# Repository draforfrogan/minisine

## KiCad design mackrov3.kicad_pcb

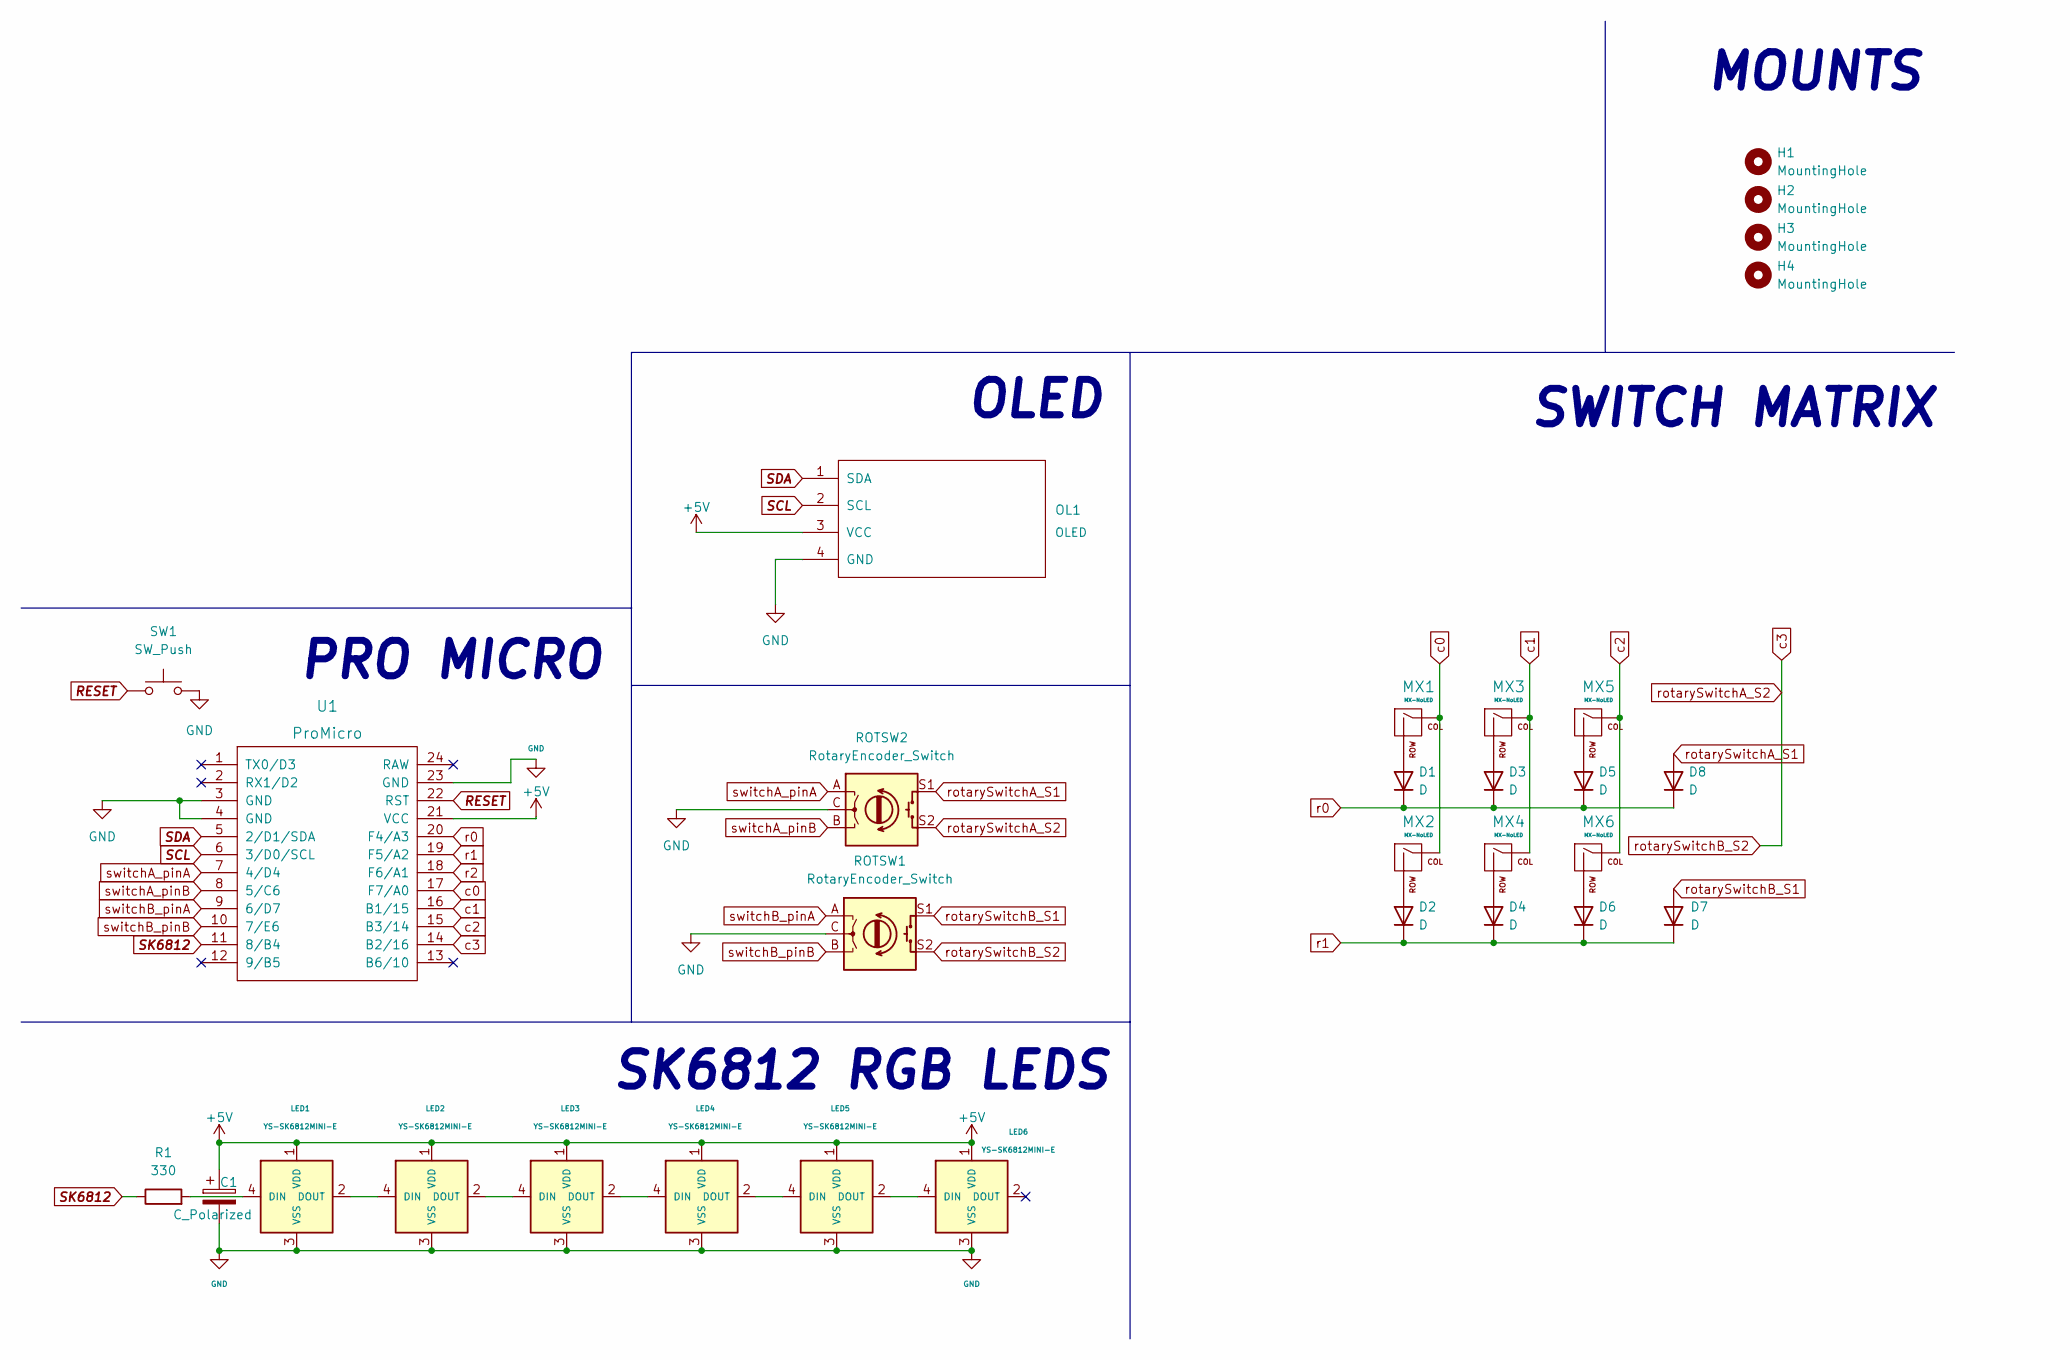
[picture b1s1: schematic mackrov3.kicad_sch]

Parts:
C1: C_Polarized; CP_Radial_D6.3mm_P2.50mm
D1, D2, D3, D4, D5, D6, D7, D8: D; DIODE NO K
H1, H2, H3, H4: MountingHole; MountingHole_2.2mm_M2_ISO7380
LED1, LED2, LED3, LED4, LED5, LED6: YS-SK6812MINI-E
MX1, MX2, MX3, MX4, MX5, MX6: MX-NoLED; CherryMX_Hotswap
OL1: OLED; OLED_v2
R1: 330; R_Axial_DIN0204_L3.6mm_D1.6mm_P5.08mm_Horizontal
ROTSW1: RotaryEncoder_Switch; RotaryEncoder_Alps_EC11E-Switch_Vertical_H20mm_CircularMoun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
ROTSW2: RotaryEncoder_Switch; RotaryEncoder_Alps_EC11E-Switch_Vertical_H20mm
SW1: SW_Push; SW_PUSH_6mm
U1: ProMicro; ProMicro_v3.5 USB C

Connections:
+5V: C1.1, LED1.1 (VDD), LED2.1 (VDD), LED3.1 (VDD), LED4.1 (VDD), LED5.1 (VDD), LED6.1 (VDD), OL1.3 (VCC), U1.21 (VCC)
GND: C1.2, LED1.3 (VSS), LED2.3 (VSS), LED3.3 (VSS), LED4.3 (VSS), LED5.3 (VSS), LED6.3 (VSS), OL1.4 (GND), ROTSW1.C, ROTSW2.C, SW1.2, U1.3 (GND), U1.4 (GND), U1.23 (GND); also elsewhere on the board
unnamed: D1.2 (A), MX1.2 (ROW)
unnamed: D2.2 (A), MX2.2 (ROW)
unnamed: D3.2 (A), MX3.2 (ROW)
unnamed: D4.2 (A), MX4.2 (ROW)
unnamed: D5.2 (A), MX5.2 (ROW)
unnamed: D6.2 (A), MX6.2 (ROW)
unnamed: LED1.2 (DOUT), LED2.4 (DIN)
unnamed: LED1.4 (DIN), R1.2
unnamed: LED2.2 (DOUT), LED3.4 (DIN)
unnamed: LED3.2 (DOUT), LED4.4 (DIN)
unnamed: LED4.2 (DOUT), LED5.4 (DIN)
unnamed: LED5.2 (DOUT), LED6.4 (DIN)
RESET: SW1.1, U1.22 (RST); also elsewhere on the board
SCL: OL1.2 (SCL), U1.6 (3/D0/SCL)
SDA: OL1.1 (SDA), U1.5 (2/D1/SDA)
SK6812: R1.1, U1.11 (8/B4)
c0: MX1.1 (COL), MX2.1 (COL), U1.17 (F7/A0)
c1: MX3.1 (COL), MX4.1 (COL), U1.16 (B1/15)
c2: MX5.1 (COL), MX6.1 (COL), U1.15 (B3/14)
r0: D1.1 (K), D3.1 (K), D5.1 (K), D8.1 (K), U1.20 (F4/A3)
r1: D2.1 (K), D4.1 (K), D6.1 (K), D7.1 (K), U1.19 (F5/A2)
r2: U1.18 (F6/A1)
rotarySwitchA_S1: D8.2 (A), ROTSW2.S1
rotarySwitchA_S2: ROTSW1.S2, ROTSW2.S2, U1.14 (B2/16)
rotarySwitchB_S1: D7.2 (A), ROTSW1.S1
switchA_pinA: ROTSW2.A, U1.7 (4/D4)
switchA_pinB: ROTSW2.B, U1.8 (5/C6)
switchB_pinA: ROTSW1.A, U1.9 (6/D7)
switchB_pinB: ROTSW1.B, U1.10 (7/E6)

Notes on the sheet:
SK6812 RGB LEDS
SWITCH MATRIX
PRO MICRO
OLED
MOUNTS

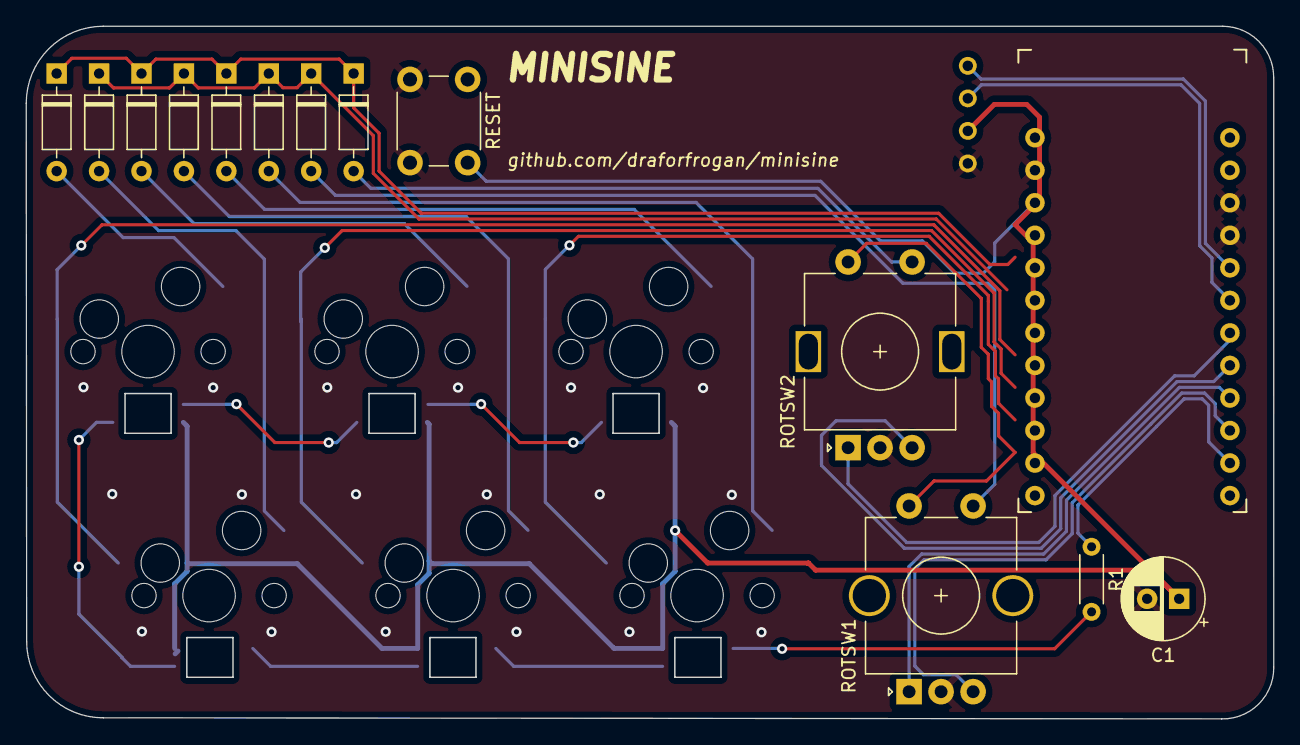
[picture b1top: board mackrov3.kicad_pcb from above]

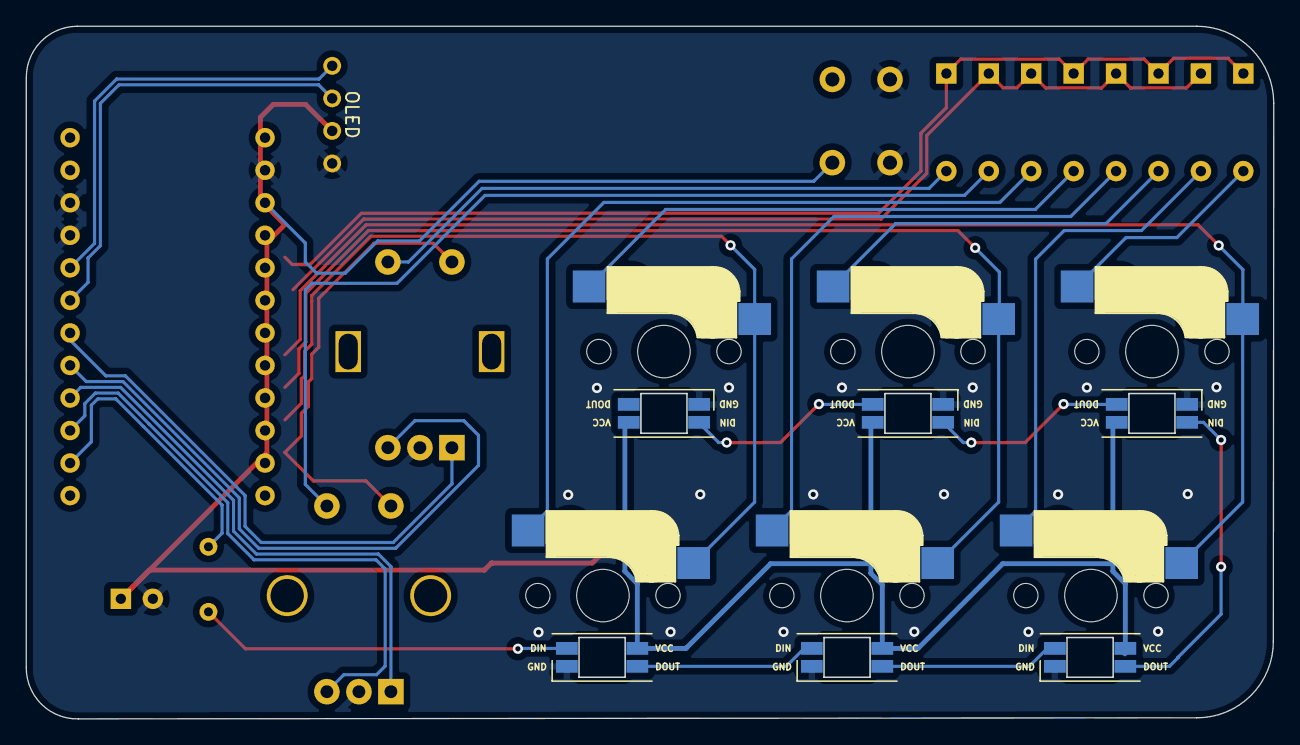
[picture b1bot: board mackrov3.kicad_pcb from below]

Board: 2 copper layers, 97.4 x 54.1 mm, 31 parts (7 on the bottom side), 30 nets.

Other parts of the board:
RESET: SW_Push; SW_PUSH_6mm

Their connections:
GND: RESET.2; also elsewhere on the board
RESET: RESET.1; also elsewhere on the board

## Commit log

2022-02-04 Add KiCAD hardware files
2022-02-05 Add updates
